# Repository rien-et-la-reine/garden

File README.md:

# garden
a split 56 key columnar stagger keyboard with a tentable thumb cluster [WIP]

ZMK support using nice!nano v2: https://github.com/rien-et-la-reine/garden-path

*note: do NOT disconnect trrs connectors while power on, the way they are used here won't short VCC to ground or anything, but will short some columns/rows with each other which could be potentially damaging

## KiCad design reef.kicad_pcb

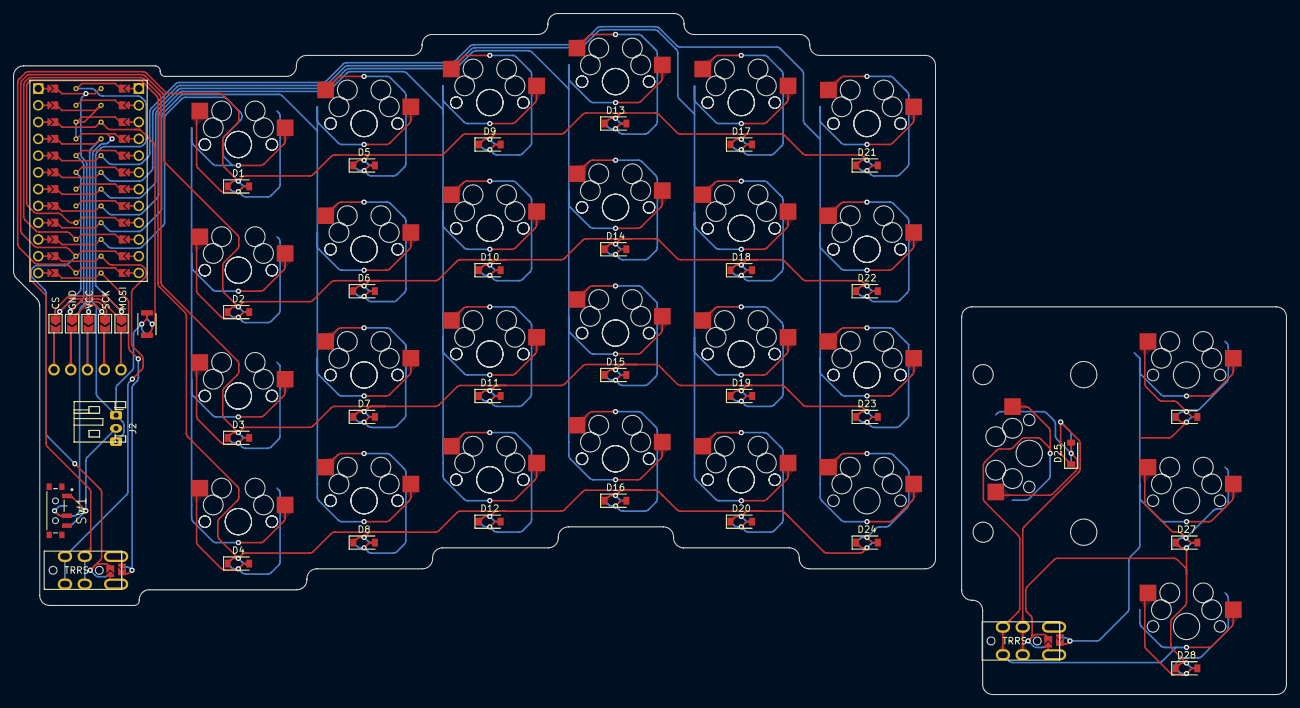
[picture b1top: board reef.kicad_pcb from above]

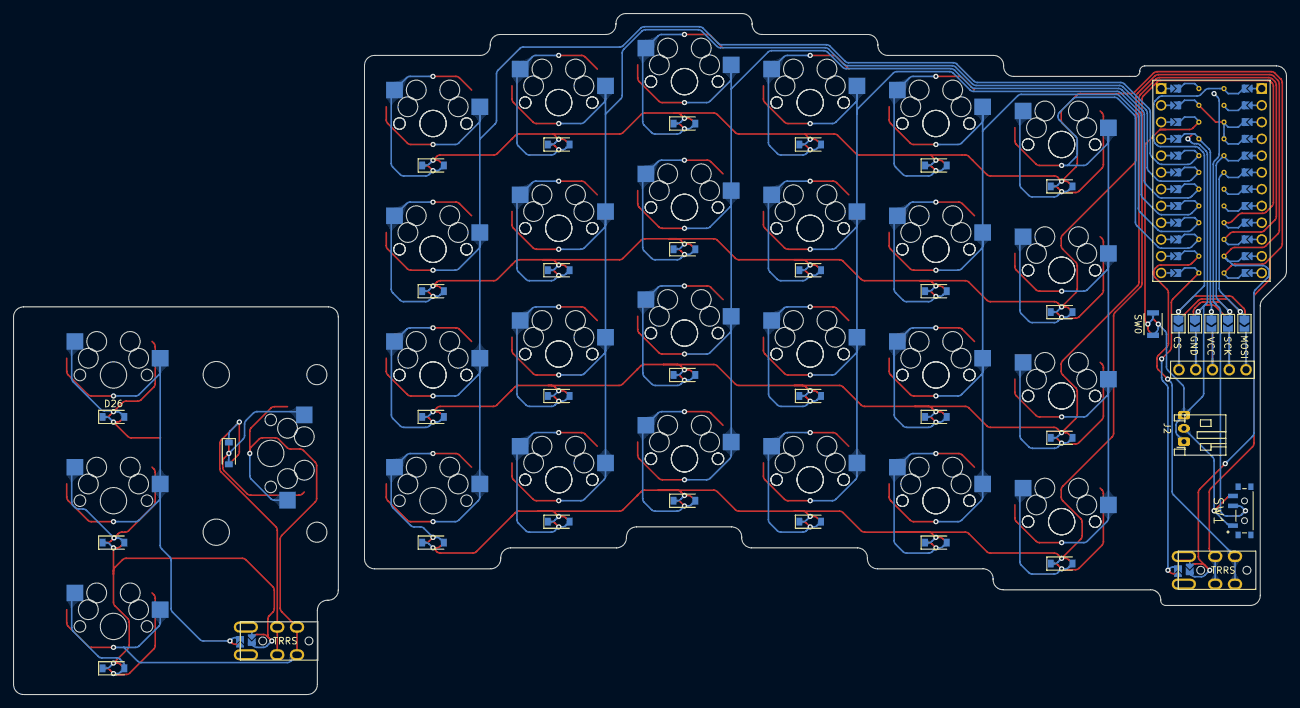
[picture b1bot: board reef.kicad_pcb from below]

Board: 2 copper layers, 192.9 x 103.2 mm, 87 parts (29 on the bottom side), 57 nets.

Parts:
D1, D2, D3, D4, D5, D6, D7, D8, D9, D10, D11, D12, D13, D14, D15, D16, D17, D18, D19, D20, D21, D22, D23, D24, D25, D26, D27, D28: D_Small; D_SOD-123_reversible
Display1: nice!view; nice_view_adapted
J1: nice!view sockets; nice_view_adapted
J2: battery connector; JST_PH_S2B-PH-K_1x02_P2.00mm_Horizontal
MX1, MX1#2, MX2, MX2#2, MX3, MX3#2, MX4, MX4#2, MX5, MX5#2, MX6, MX6#2, MX7, MX7#2, MX8, MX8#2, MX9, MX9#2, MX10, MX10#2, MX11, MX11#2, MX12, MX12#2, MX13, MX13#2, MX14, MX14#2, MX15, MX15#2, MX16, MX16#2, MX17, MX17#2, MX18, MX18#2, MX19, MX19#2, MX20, MX20#2, MX21, MX21#2, MX22, MX22#2, MX23, MX23#2, MX24: MX-NoLED; MXOnly-1U-Hotswap
MX25: MX-NoLED; MXOnly-2.25U-Hotswap
MX26, MX27, MX28: MX-NoLED; MXOnly-1.5U-Hotswap
SW0: B3U-1000P[]; SW_B3U-1000P_OMR
SW1: PCM12SMTR; SW_PCM12SMTR
U1: nice_nano; ProMicro
U2, U3: TRRS; PJ-320A

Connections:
unnamed: D1.2 (A), MX1.2 (ROW), MX1#2.2 (ROW)
unnamed: D2.2 (A), MX2.2 (ROW), MX2#2.2 (ROW)
unnamed: D3.2 (A), MX3.2 (ROW), MX3#2.2 (ROW)
unnamed: D4.2 (A), MX4.2 (ROW), MX4#2.2 (ROW)
unnamed: D5.2 (A), MX5.2 (ROW), MX5#2.2 (ROW)
unnamed: D6.2 (A), MX6.2 (ROW), MX6#2.2 (ROW)
unnamed: D7.2 (A), MX7.2 (ROW), MX7#2.2 (ROW)
unnamed: D8.2 (A), MX8.2 (ROW), MX8#2.2 (ROW)
unnamed: D9.2 (A), MX9.2 (ROW), MX9#2.2 (ROW)
unnamed: D10.2 (A), MX10.2 (ROW), MX10#2.2 (ROW)
unnamed: D11.2 (A), MX11.2 (ROW), MX11#2.2 (ROW)
unnamed: D12.2 (A), MX12.2 (ROW), MX12#2.2 (ROW)
unnamed: D13.2 (A), MX13.2 (ROW), MX13#2.2 (ROW)
unnamed: D14.2 (A), MX14.2 (ROW), MX14#2.2 (ROW)
unnamed: D15.2 (A), MX15.2 (ROW), MX15#2.2 (ROW)
unnamed: D16.2 (A), MX16.2 (ROW), MX16#2.2 (ROW)
unnamed: D17.2 (A), MX17.2 (ROW), MX17#2.2 (ROW)
unnamed: D18.2 (A), MX18.2 (ROW), MX18#2.2 (ROW)
unnamed: D19.2 (A), MX19.2 (ROW), MX19#2.2 (ROW)
unnamed: D20.2 (A), MX20.2 (ROW), MX20#2.2 (ROW)
unnamed: D21.2 (A), MX21.2 (ROW), MX21#2.2 (ROW)
unnamed: D22.2 (A), MX22.2 (ROW), MX22#2.2 (ROW)
unnamed: D23.2 (A), MX23.2 (ROW), MX23#2.2 (ROW)
unnamed: D24.2 (A), MX24.2 (ROW)
unnamed: D25.2 (A), MX25.2 (ROW)
unnamed: D26.2 (A), MX26.2 (ROW)
unnamed: D27.2 (A), MX27.2 (ROW)
unnamed: D28.2 (A), MX28.2 (ROW)
bat+: SW1.2, U1.24 (BATIN/P0.04)
bat_sw+: J2.2, SW1.1
col_0: MX1.1 (COL), MX1#2.1 (COL), MX2.1 (COL), MX2#2.1 (COL), MX3.1 (COL), MX3#2.1 (COL), MX4.1 (COL), MX4#2.1 (COL), U1.15 (P1.11)
col_1: MX5.1 (COL), MX5#2.1 (COL), MX6.1 (COL), MX6#2.1 (COL), MX7.1 (COL), MX7#2.1 (COL), MX8.1 (COL), MX8#2.1 (COL), U1.16 (P1.13)
col_2: MX9.1 (COL), MX9#2.1 (COL), MX10.1 (COL), MX10#2.1 (COL), MX11.1 (COL), MX11#2.1 (COL), MX12.1 (COL), MX12#2.1 (COL), U1.17 (P1.15)
col_3: MX13.1 (COL), MX13#2.1 (COL), MX14.1 (COL), MX14#2.1 (COL), MX15.1 (COL), MX15#2.1 (COL), MX16.1 (COL), MX16#2.1 (COL), U1.18 (AIN0/P0.02)
col_4: MX17.1 (COL), MX17#2.1 (COL), MX18.1 (COL), MX18#2.1 (COL), MX19.1 (COL), MX19#2.1 (COL), MX20.1 (COL), MX20#2.1 (COL), U1.19 (AIN5/P0.29)
col_5: MX21.1 (COL), MX21#2.1 (COL), MX22.1 (COL), MX22#2.1 (COL), MX23.1 (COL), MX23#2.1 (COL), MX24.1 (COL), U1.20 (AIN7/P0.31)
col_6: U1.14 (NFC2/P0.10), U2.4 (RING2)
col_7: U1.13 (NFC1/P0.09), U2.1 (SLEEVE)
cs: J1.5, U1.1 (TX0/P0.06)
disp_1: Display1.1, J1.6, J1.10
disp_2: Display1.2, J1.7, J1.9
disp_3: Display1.3, J1.8
disp_4: Display1.4, J1.7, J1.9
disp_5: Display1.5, J1.6, J1.10
gnd: J1.4, J2.1, SW0.1, U1.3 (GND), U1.4 (GND), U1.23 (GND)
mosi: J1.1, U1.6 (P0.20)
row_0: D1.1 (K), D5.1 (K), D9.1 (K), D13.1 (K), D17.1 (K), D21.1 (K), U1.12 (P1.06), U2.3 (RING1)
row_1: D2.1 (K), D6.1 (K), D10.1 (K), D14.1 (K), D18.1 (K), D22.1 (K), U1.11 (P1.04), U2.2 (TIP)
row_2: D3.1 (K), D7.1 (K), D11.1 (K), D15.1 (K), D19.1 (K), D23.1 (K), U1.10 (P0.11)
row_3: D4.1 (K), D8.1 (K), D12.1 (K), D16.1 (K), D20.1 (K), D24.1 (K), U1.9 (P1.00)
rst: SW0.2, U1.22 (RST)
sck: J1.2, U1.5 (P0.17)
thc_6: MX25.1 (COL), MX28.1 (COL), U3.4 (RING2)
thc_7: MX26.1 (COL), MX27.1 (COL), U3.1 (SLEEVE)
thr_0: D25.1 (K), D26.1 (K), U3.3 (RING1)
thr_1: D27.1 (K), D28.1 (K), U3.2 (TIP)
vcc: J1.3, U1.21 (VCC)

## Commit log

2023-08-12 init
    initialise README and LICENSE
2023-08-12 init KiCAD project
    created the KiCAD project
2023-08-12 init submodules
2023-08-12 init project libraries
    initialize symbol and footprint libraries into KiCAD project
2023-08-12 adjust nicenano module
2023-08-18 additional config
2023-08-19 schematic complete
    finished schematic, assigned footprints for most components (except connectors)
2023-08-20 update connectors
    update board and thumb cluster conectors (using SF7381-5PG-3ES 5 pin panel mount connector)
2023-08-20 Connector Change
    switching to slightly smaller T4140012051-000 connector.
2023-08-20 init PCB
    initialise PCB from schematic
2023-08-20 cleanup
    removing unused and unnecessary files
2023-08-20 PCB Layout
    layout of keys, controller board, connectors + routed matrix columns
2023-08-20 PCB updates + importing keebio library
2023-08-20 Importing Keebio part libraries
    mostly for the TRRS port
2023-08-21 Updated Layout
    modified layout to use trrs to connect with thumb cluster, added connector for battery, and footprint for nice!view display
2023-08-21 Flipside Linkage
    connected diode pads to their flipside counterparts, thumb cluster should now be fully routed, to be ground-planed later
2023-08-21 Thumb Cluster Routing
    thumb cluster routing should NOW be complete (rows were not connected up previously)
2023-08-21 Matrix Routing
    Routing for the switch matrix (including some things missed from the thumb cluster yet again) should now be complete
2023-08-21 Route Display
    Display connected to nice!nano. in order to keep pcb reversible, jumper wire will be soldered between the actual display pad footprint and the appropriate column of pads (J1)
2023-08-22 new submodule for reversible footprints
2023-08-22 Reversible via Jumper Pads
    using solder jumper pads to make component footprints reversible
2023-08-22 Display Routing
    Traces for display should no longer interfere with routing columns and rows to their respective pins in an aesthetically pleasing manner...hopefully
2023-08-22 Matrix Reroute
    rerouted some matrix traces to connect to vias instead of going through diode pads
2023-08-22 Remove Unused Library
    removing now unused library for m12 5 pin connector
2023-08-22 Routed Battery Connector
    routed traces for battery connector
2023-08-22 Reset and Power switches in progress
2023-08-22 reverting
2023-08-22 Power and Reset switch symbols and footprints
2023-08-23 Power and Reset schematics
    added power and reset switches to schematic
2023-08-23 Power and Reset footprints
    added footprints for power and reset switches to PCB
2023-08-23 Reset, Power, Battery
    routed reset switch, power switch, battery connector
2023-08-23 Ports and Switches
    rerouted reset switch, routed trrs connector. all switches and ports should now be routed
2023-08-23 Layout
    arranged everything in rough layout of final board
2023-08-23 Traces Routed
    all traces should now be fully routed
2023-08-23 Teardrops and Fillets
2023-08-23 Ground Fill
    added ground fill to front and back copper layers (to hopefully mitigate any potential interference that might occur)
2023-08-23 Ground Fillet
    filleted ground plane zones
2023-08-23 Zone Clearance
    increased zone minimum clearance to prevent overlap of ground fill with teardrops
2023-08-23 Wiping Away Tears
2023-08-23 Teardrops and Edge Cuts
    migrated to KiCAD v7, added back teardrops and edgecuts
2023-08-23 Ground Fill and Mousebites
    attached thumb cluster to main board with mousebites, added back ground fill
2023-08-23 Delete keebio-components
    removing unused submodule
2023-08-23 Ground Stitching
    stitching together ground pours with freestanding vias
2023-08-24 Rotated TRRS Port
    rotated the TRRS port on the main board to face the bottom (will make it easier to connect to the thumb cluster)
2023-08-24 Mounting Holes
    added holes for M2 standoffs for mounting to a bottom plate. went a little overboard with the holes, revision 2 of this board will only keep the ones needed
2023-08-25 rename
2024-03-29 generated drill files
2024-03-29 cleanup
    removing gerber and drill files
